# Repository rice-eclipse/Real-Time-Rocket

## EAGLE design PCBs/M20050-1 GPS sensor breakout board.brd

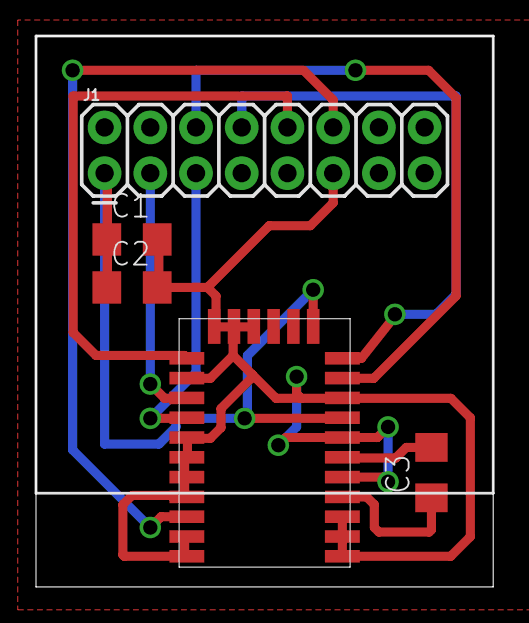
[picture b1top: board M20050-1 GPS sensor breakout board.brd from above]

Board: 2 copper layers, 25.4 x 30.6 mm, 5 parts (0 on the bottom side), 10 nets.

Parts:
A1: M20050-1_GPS
C1, C2, C3: 22 pF; C1206
J1: 2X6 FEMALE; 2X7

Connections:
GND: A1.P1, A1.P2, A1.P3, A1.P5, A1.P7, A1.P9, A1.P15, A1.P16, A1.P17, A1.P19, A1.P22, A1.P23, A1.P24, A1.P25, A1.P27, A1.P28, C1.2, C2.2, J1.11
unnamed: A1.P8, A1.P12, C1.1, C2.1, J1.1
unnamed: A1.P20, J1.3
unnamed: A1.P21, J1.5
unnamed: A1.P4, C3.1
unnamed: A1.P6, C3.2
unnamed: A1.P26, J1.12
unnamed: A1.P18, J1.10
unnamed: A1.P11, J1.8
unnamed: A1.P10, J1.6
